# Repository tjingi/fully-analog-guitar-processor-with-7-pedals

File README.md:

## Fishman
- This is a 7-pedal analog guitar processor!
- It features:
- Fuzz Face
- Distortion
- Overdrive
- Phaser
- Flanger
- Delay
- Chorus
Being 100% analog, it delivers a fantastic vintage sound straight out of the 80s and 90s. When designing it, I was heavily inspired by the psychedelic sound of King Gizzard & The Lizard Wizard. Since the enclosure is shaped like a fish, I named it 'Fishman'.

## CAD
- To assemble the enclosure, you will need:
- 27x M3 bolts
- To mount the PCB to the enclosure:
- 4x M3 bolts

  *Made in Fusion 360*

# PCB
Fully designed in KiCad!
<---fuzz face

<----distoshion
<-----overdrive
<----phaser
<----flanger
<----chorus
<-----delay

<---PCB

# BOM

| Component | Value | Quantity |
| :--- | :--- | :---: |
| Capacitor | 5pF | 1 |
| Capacitor | 47pF | 2 |
| Capacitor | 100pF | 4 |
| Capacitor | 150pF | 3 |
| Capacitor | 180pF | 1 |
| Capacitor | 220pF | 2 |
| Capacitor | 330pF | 1 |
| Capacitor | 470pF | 1 |
| Capacitor | 1nF | 4 |
| Capacitor | 2.2nF | 2 |
| Capacitor | 2.7nF | 1 |
| Capacitor | 3.3nF | 1 |
| Capacitor | 3.9nF | 1 |
| Capacitor | 4.7nF | 2 |
| Capacitor | 6.8nF | 2 |
| Capacitor | 8.2nF | 1 |
| Capacitor | 10nF | 11 |
| Capacitor | 12nF | 1 |
| Capacitor | 15nF | 1 |
| Capacitor | 22nF | 2 |
| Capacitor | 33nF | 2 |
| Capacitor | 47nF | 13 |
| Capacitor | 100nF | 6 |
| Capacitor | 220nF | 1 |
| Capacitor | 330nF | 1 |
| Capacitor | 0.47uF | 2 |
| Capacitor | 1uF | 13 |
| Capacitor | 2.2uF | 1 |
| Capacitor | 10uF | 3 |
| Capacitor | 15uF | 1 |
| Capacitor | 20uF | 1 |
| Capacitor | 22uF | 2 |
| Capacitor | 33uF | 3 |
| Capacitor | 47uF | 5 |
| Capacitor | 100uF | 3 |
| Resistor | 33 Ohm | 1 |
| Resistor | 330 Ohm | 1 |
| Resistor | 470 Ohm | 1 |
| Resistor | 1k | 14 |
| Resistor | 1.5k | 1 |
| Resistor | 2k | 1 |
| Resistor | 2.7k | 1 |
| Resistor | 3.3k | 1 |
| Resistor | 4.7k | 8 |
| Resistor | 5.1k | 1 |
| Resistor | 6.8k | 4 |
| Resistor | 10k | 42 |
| Resistor | 12k | 2 |
| Resistor | 20k | 2 |
| Resistor | 22k | 3 |
| Resistor | 24k | 4 |
| Resistor | 27k | 2 |
| Resistor | 33k | 9 |
| Resistor | 39k | 4 |
| Resistor | 47k | 8 |
| Resistor | 56k | 2 |
| Resistor | 68k | 2 |
| Resistor | 82k | 2 |
| Resistor | 100k | 7 |
| Resistor | 120k | 1 |
| Resistor | 150k | 7 |
| Resistor | 180k | 3 |
| Resistor | 220k | 6 |
| Resistor | 330k | 2 |
| Resistor | 360k | 1 |
| Resistor | 470k | 6 |
| Resistor | 1M | 9 |
| Resistor | 2.2M | 1 |
| Resistor | 3.9M | 1 |
| Potentiometer (Alpha) | 10k | 1 |
| Potentiometer (Alpha) | 1M | 1 |
| Potentiometer (Alpha) | A25k | 1 |
| Potentiometer (Alpha) | A50k | 1 |
| Potentiometer (Alpha) | A100k | 1 |
| Potentiometer (Alpha) | A500k | 1 |
| Potentiometer (Alpha) | B1k | 1 |
| Potentiometer (Alpha) | B10k | 1 |
| Potentiometer (Alpha) | B50k | 5 |
| Potentiometer (Alpha) | B100k | 1 |
| Potentiometer (Alpha) | C50k | 1 |
| Potentiometer (Alpha) | C250k | 1 |
| Potentiometer (Alpha) | C500k | 2 |
| Trimmer Potentiometer (RM-065) | 20k | 2 |
| Trimmer Potentiometer (RM-065) | B50k | 1 |
| Trimmer Potentiometer (RM-065) | 100k | 1 |
| Trimmer Potentiometer (RM-065) | 250k | 1 |
| Trimmer Potentiometer (RM-065) | 500k | 1 |
| Integrated Circuit | TL062 | 1 |
| Integrated Circuit | TL071 | 3 |
| Integrated Circuit | TL072 | 1 |
| Integrated Circuit | LM358 | 1 |
| Integrated Circuit | LM741 | 6 |
| Integrated Circuit | RC4558 | 3 |
| Integrated Circuit | MN3007 | 1 |
| Integrated Circuit | MN3102 | 1 |
| Integrated Circuit | MN3207 | 1 |
| Integrated Circuit | CD4047 | 1 |
| Integrated Circuit | PT2399 | 1 |
| Voltage Regulator | L78L05 | 2 |
| Transistor | 2N3906 | 1 |
| Transistor | 2N5088 | 8 |
| Transistor | 2N5952 | 4 |
| Transistor | 2SA733 | 1 |
| Transistor | 2N2907 | 1 |
| Transistor | BC108B | 1 |
| Transistor | BC109B | 1 |
| Diode | 1N914 | 1 |
| Diode | 1N4001 | 1 |
| Diode | 1N4007 | 1 |
| Diode | 1N4148 | 12 |
| Zener Diode | BZV55B5V1 (5.1V) | 1 |
| LED | 3mm | 7 |
| Audio Jack | 6.35mm (Neutrik NRJ4HH-1) | 2 |
| DC Power Jack | Barrel Jack Switch | 1 |
| Footswitch | 3PDT | 7 |
|PCB "Fishman"| |1|
|3D printed enclosure| | 1|
|M3 screw| 25mm| 27|
|M3 screw|10mm|4|

## Assembly

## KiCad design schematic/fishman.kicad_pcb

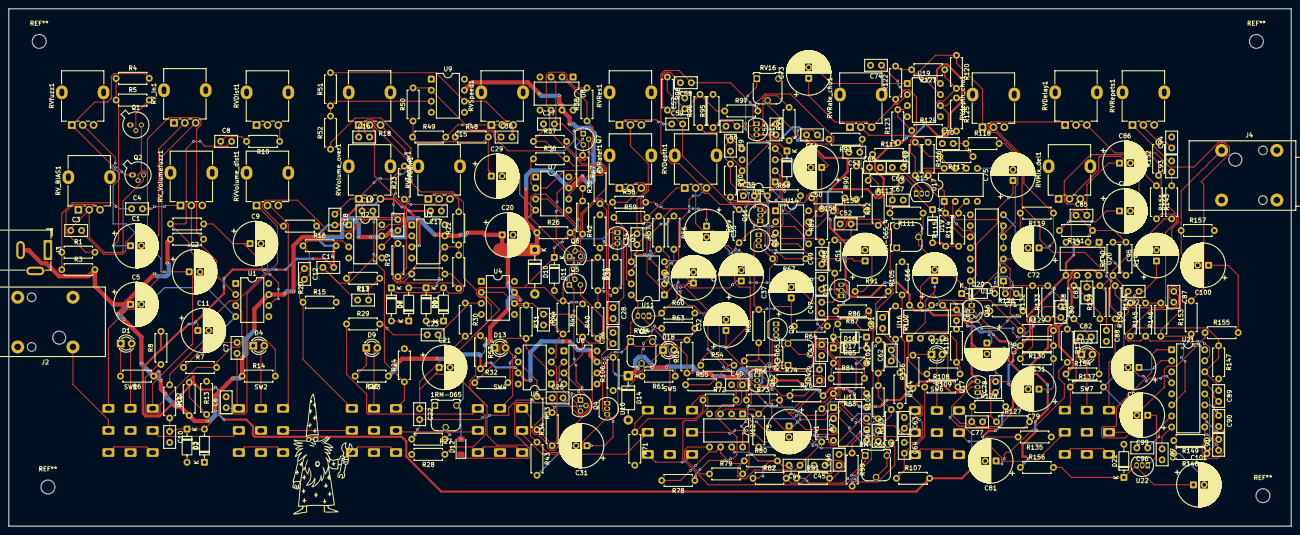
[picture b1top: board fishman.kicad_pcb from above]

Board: 2 copper layers, 295.0 x 119.0 mm, 358 parts (0 on the bottom side), 239 nets.

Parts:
1RM-065: 250K; Potentiometer_Runtron_RM-065_Vertical
C1: 0.47uF; CP_Radial_D10.0mm_P2.50mm
C2: 20uF; CP_Radial_D10.0mm_P2.50mm
C3, C45: 220p; C_Disc_D5.0mm_W2.5mm_P2.50mm
C4: 0.47uF; C_Disc_D5.0mm_W2.5mm_P2.50mm
C5, C101: 100uF; CP_Radial_D10.0mm_P2.50mm
C6, C10, C57, C92: 1n; C_Disc_D5.0mm_W2.5mm_P2.50mm
C7, C23, C30, C34: 10n; C_Disc_D5.0mm_W2.5mm_P2.50mm
C8, C22, C24, C25, C26, C27, C28, C40, C46, C59, C60, C94: 47n; C_Disc_D5.0mm_W2.5mm_P2.50mm
C9, C11, C50, C51: 1u; CP_Radial_D10.0mm_P2.50mm
C12, C13, C14, C18: 0.01uF; C_Disc_D5.0mm_W2.5mm_P2.50mm
C15, C85: 100pF; C_Disc_D5.0mm_W2.5mm_P2.50mm
C16: 0.1uF; C_Disc_D5.0mm_W2.5mm_P2.50mm
C17: 0.01uf; C_Disc_D5.0mm_W2.5mm_P2.50mm
C19: 100nF; C_Disc_D5.0mm_W2.5mm_P2.50mm
C20, C32, C33: 47u; CP_Radial_D10.0mm_P2.50mm
C21, C37: 22u; CP_Radial_D10.0mm_P2.50mm
C29: 15u; CP_Radial_D10.0mm_P2.50mm
C31: 100u; CP_Radial_D10.0mm_P2.50mm
C35, C36: 33u; CP_Radial_D10.0mm_P2.50mm
C38: 5p; C_Disc_D5.0mm_W2.5mm_P2.50mm
C39: 47p; C_Disc_D5.0mm_W2.5mm_P2.50mm
C41: 33uF; CP_Radial_D10.0mm_P2.50mm
C42: 1uf; C_Disc_D5.0mm_W2.5mm_P2.50mm
C43, C61: 6n8; C_Disc_D5.0mm_W2.5mm_P2.50mm
C44, C62: 100p; C_Disc_D5.0mm_W2.5mm_P2.50mm
C47: 12n; C_Disc_D5.0mm_W2.5mm_P2.50mm
C48, C58: 150p; C_Disc_D5.0mm_W2.5mm_P2.50mm
C49, C52: 33n; C_Disc_D5.0mm_W2.5mm_P2.50mm
C53: 3n9; C_Disc_D5.0mm_W2.5mm_P2.50mm
C54: 8n2; C_Disc_D5.0mm_W2.5mm_P2.50mm
C55: 330p; C_Disc_D5.0mm_W2.5mm_P2.50mm
C56: 220n; C_Disc_D5.0mm_W2.5mm_P2.50mm
C63: 1uF; C_Disc_D5.0mm_W2.5mm_P2.50mm
C64: 0.33; C_Disc_D5.0mm_W2.5mm_P2.50mm
C65, C80: 0.01; C_Disc_D5.0mm_W2.5mm_P2.50mm
C66: 1uf; CP_Radial_D10.0mm_P2.50mm
C67: 0.0033; C_Disc_D5.0mm_W2.5mm_P2.50mm
C68: 0.015; C_Disc_D5.0mm_W2.5mm_P2.50mm
C69: 470pF; C_Disc_D5.0mm_W2.5mm_P2.50mm
C70: 0.0047; C_Disc_D5.0mm_W2.5mm_P2.50mm
C71: 150pF; C_Disc_D5.0mm_W2.5mm_P2.50mm
C72, C75, C76: 10uF; CP_Radial_D10.0mm_P2.50mm
C73: 2.2uF; CP_Radial_D10.0mm_P2.50mm
C74: 0.047; C_Disc_D5.0mm_W2.5mm_P2.50mm
C77: 0.0027; C_Disc_D5.0mm_W2.5mm_P2.50mm
C78: 180pF; C_Disc_D5.0mm_W2.5mm_P2.50mm
C79, C81, C84, C86, C95: 1uF; CP_Radial_D10.0mm_P2.50mm
C82, C93: 22n; C_Disc_D5.0mm_W2.5mm_P2.50mm
C83: 47pF; C_Disc_D5.0mm_W2.5mm_P2.50mm
C87, C89: 2n2; C_Disc_D5.0mm_W2.5mm_P2.50mm
C88: 4n7; C_Disc_D5.0mm_W2.5mm_P2.50mm
C90, C91, C96, C97: 100n; C_Disc_D5.0mm_W2.5mm_P2.50mm
C98, C99: 47uF; CP_Radial_D10.0mm_P2.50mm
C100: C_Polarized; CP_Radial_D10.0mm_P2.50mm
D1, D4, D9, D13, D18, D21, D23: LED; LED_D3.0mm
D2, D3, D5, D6, D7, D8, D15, D16, D17, D19, D20, D22: 1N4148; D_DO-35_SOD27_P7.62mm_Horizontal
D10: 1N4007; D_DO-41_SOD81_P10.16mm_Horizontal
D11: 1N914; D_DO-35_SOD27_P7.62mm_Horizontal
D12: BZV55B5V1; D_MiniMELF
D14: 1N4001; D_DO-41_SOD81_P10.16mm_Horizontal
J2, J4: NRJ4HH-1; Jack_6.35mm_Neutrik_NRJ4HH-1_Horizontal
J3: Barrel_Jack_Switch; BarrelJack_GCT_DCJ200-10-A_Horizontal
Q1: BC108B; TO-18-3
Q2: BC109B; TO-18-3
Q3: 2N3906; TO-92_Inline
Q4, Q5, Q6, Q7: 2n5952; TO-92
Q8, Q9, Q10, Q12, Q13, Q14, Q16, Q17: 2n5088; TO-92_Inline
Q11: 2SA733; TO-92_Inline
Q15: 2n2907; TO-92_Inline
R1, R10: 4.7K; R_Axial_DIN0207_L6.3mm_D2.5mm_P7.62mm_Horizontal
R2: 33k; R_Axial_DIN0207_L6.3mm_D2.5mm_P7.62mm_Horizontal
R3: 330; R_Axial_DIN0207_L6.3mm_D2.5mm_P7.62mm_Horizontal
R4, R56, R89, R105, R135, R144, R157: 100K; R_Axial_DIN0207_L6.3mm_D2.5mm_P7.62mm_Horizontal
R5, R6, R14, R22, R25, R53, R72, R106, R108, R134, R136, R143, R154, R155: 1K; R_Axial_DIN0207_L6.3mm_D2.5mm_P7.62mm_Horizontal
R7, R11, R19, R26, R29, R31, R32, R33, R34, R35, R36, R37, R38, R54, R55, R76, R77, R79, R83, R86, R87, R88, R92, R93, R94, R95, R102, R112, R113, R116, R117, R126, R128, R131, R145, R146, R148, R149, R150, R158, R159, R160: 10K; R_Axial_DIN0207_L6.3mm_D2.5mm_P7.62mm_Horizontal
R8, R12, R13, R16, R24, R27, R28, R71, R137: 1M; R_Axial_DIN0207_L6.3mm_D2.5mm_P7.62mm_Horizontal
R9, R30, R51, R61, R73, R121: 470K; R_Axial_DIN0207_L6.3mm_D2.5mm_P7.62mm_Horizontal
R15: 2.2M; R_Axial_DIN0207_L6.3mm_D2.5mm_P7.62mm_Horizontal
R17, R69, R70, R74, R75, R109, R114, R132: 33K; R_Axial_DIN0207_L6.3mm_D2.5mm_P7.62mm_Horizontal
R18, R100: 27K; R_Axial_DIN0207_L6.3mm_D2.5mm_P7.62mm_Horizontal
R20, R23, R110: 6.8K; R_Axial_DIN0207_L6.3mm_D2.5mm_P7.62mm_Horizontal
R21, R57, R64, R81, R107, R130: 220K; R_Axial_DIN0207_L6.3mm_D2.5mm_P7.62mm_Horizontal
R39, R40, R41, R43, R50, R52, R62: 150K; R_Axial_DIN0207_L6.3mm_D2.5mm_P7.62mm_Horizontal
R42, R90: 56K; R_Axial_DIN0207_L6.3mm_D2.5mm_P7.62mm_Horizontal
R44, R45, R46, R47: 24K; R_Axial_DIN0207_L6.3mm_D2.5mm_P7.62mm_Horizontal
R48: 3M9; R_Axial_DIN0207_L6.3mm_D2.5mm_P7.62mm_Horizontal
R49, R60, R65, R67, R68, R85: 4K7; R_Axial_DIN0207_L6.3mm_D2.5mm_P7.62mm_Horizontal
R58: 1K5; R_Axial_DIN0207_L6.3mm_D2.5mm_P7.62mm_Horizontal
R59, R123, R138: 180K; R_Axial_DIN0207_L6.3mm_D2.5mm_P7.62mm_Horizontal
R63, R124: 68K; R_Axial_DIN0207_L6.3mm_D2.5mm_P7.62mm_Horizontal
R66, R91: 330K; R_Axial_DIN0207_L6.3mm_D2.5mm_P7.62mm_Horizontal
R78, R80, R84, R96, R98, R101, R103, R122: 47K; R_Axial_DIN0207_L6.3mm_D2.5mm_P7.62mm_Horizontal
R82, R125: 82K; R_Axial_DIN0207_L6.3mm_D2.5mm_P7.62mm_Horizontal
R97: 22k; R_Axial_DIN0207_L6.3mm_D2.5mm_P7.62mm_Horizontal
R99, R118, R119, R127: 39K; R_Axial_DIN0207_L6.3mm_D2.5mm_P7.62mm_Horizontal
R104: 470R; R_Axial_DIN0207_L6.3mm_D2.5mm_P7.62mm_Horizontal
R111: 3K3; R_Axial_DIN0207_L6.3mm_D2.5mm_P7.62mm_Horizontal
R115, R142: 12K; R_Axial_DIN0207_L6.3mm_D2.5mm_P7.62mm_Horizontal
R120: 120K; R_Axial_DIN0207_L6.3mm_D2.5mm_P7.62mm_Horizontal
R129, R140: 22K; R_Axial_DIN0207_L6.3mm_D2.5mm_P7.62mm_Horizontal
R133: 6K8; R_Axial_DIN0207_L6.3mm_D2.5mm_P7.62mm_Horizontal
R139: 360K; R_Axial_DIN0207_L6.3mm_D2.5mm_P7.62mm_Horizontal
R141, R147: 20K; R_Axial_DIN0207_L6.3mm_D2.5mm_P7.62mm_Horizontal
R151: 5K1; R_Axial_DIN0207_L6.3mm_D2.5mm_P7.62mm_Horizontal
R152: 2K; R_Axial_DIN0207_L6.3mm_D2.5mm_P7.62mm_Horizontal
R153: 2K7; R_Axial_DIN0207_L6.3mm_D2.5mm_P7.62mm_Horizontal
R156: 33; R_Axial_DIN0207_L6.3mm_D2.5mm_P7.62mm_Horizontal
RM-065_2: 500K; Potentiometer_Runtron_RM-065_Vertical
RM-065_3: 20K; Potentiometer_Runtron_RM-065_Vertical
RM-065_4: 100K; Potentiometer_Runtron_RM-065_Vertical
RV14: B50K; Potentiometer_Runtron_RM-065_Vertical
RV16: 20K; Potentiometer_Runtron_RM-065_Vertical
RVDelay1: B50K; Potentiometer_Alpha_RD901F-40-00D_Single_Vertical
RVDepth1: B50K; Potentiometer_Alpha_RD901F-40-00D_Single_Vertical
RVDist1: C500K; Potentiometer_Alpha_RD901F-40-00D_Single_Vertical
RVGain1: B100K; Potentiometer_Alpha_RD901F-40-00D_Single_Vertical
RVMix_del1: B50K; Potentiometer_Alpha_RD901F-40-00D_Single_Vertical
RVRate_cho1: 1M; Potentiometer_Alpha_RD901F-40-00D_Single_Vertical
RVRatef1: C250K; Potentiometer_Alpha_RD901F-40-00D_Single_Vertical
RVRepets1: B50K; Potentiometer_Alpha_RD901F-40-00D_Single_Vertical
RVRes1: C50K; Potentiometer_Alpha_RD901F-40-00D_Single_Vertical
RVSpeed1: C500K; Potentiometer_Alpha_RD901F-40-00D_Single_Vertical
RVTone_ov1: A25K; Potentiometer_Alpha_RD901F-40-00D_Single_Vertical
RVVolume_dist1: A50K; Potentiometer_Alpha_RD901F-40-00D_Single_Vertical
RVVolume_over1: A100K; Potentiometer_Alpha_RD901F-40-00D_Single_Vertical
RV_BIAS1: B10K; Potentiometer_Alpha_RD901F-40-00D_Single_Vertical
RV_In1: B50K; Potentiometer_Alpha_RD901F-40-00D_Single_Vertical
RV_Volumefuzz1: A500K; Potentiometer_Alpha_RD901F-40-00D_Single_Vertical
RVdepth_cho1: 10K; Potentiometer_Alpha_RD901F-40-00D_Single_Vertical
RVfuzz1: B1K; Potentiometer_Alpha_RD901F-40-00D_Single_Vertical
SW1, SW2, SW3, SW4, SW5, SW6, SW7: 3PTD
U1, U2, U3: TL071; DIP-8_W7.62mm
U4, U5, U6, U7, U8, U9: LM741; DIP-8_W7.62mm
U10, U22: L78L05_TO92; TO-92_Inline
U11: TL062; DIP-8_W7.62mm
U12, U13, U16: RC4558; DIP-8_W7.62mm
U14: MN3207; DIP-8_W7.62mm
U15: MN3102; DIP-8_W7.62mm
U17: MN3007; DIP-8_W7.62mm
U18: 4047; DIP-14_W7.62mm
U19: LM358; DIP-8_W7.62mm
U20: TL072; DIP-8_W7.62mm
U21: PT2399; DIP-16_W7.62mm
o: LOGO

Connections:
67: C41.1, R73.2, R74.2, R75.1, R79.2, R83.2, R91.2, U12.3 (+), U13.3 (+)
+4.5: C11.1, C14.2, C17.2, C18.2, C65.1, R8.2, R12.2, R13.1, R16.2, R107.2, R130.2, RVVolume_over1.3, U3.3 (+), U16.5 (+), U20.3 (+), U20.5 (+)
+5V: C32.1, Q8.3 (C), Q11.1 (E), R54.1, R62.1, R69.1, RM-065_2.1, RV14.1, RV16.1, U10.1 (VO), U11.8 (V+), U14.5 (VDD), U15.1 (VDD)
+9V: C5.1, C20.1, C31.1, D10.1 (K), D14.1 (K), J3.2, Q12.3 (C), Q13.3 (C), Q14.3 (C), Q16.3 (C), Q17.3 (C), R2.1, R3.2, R6.1, R12.1, R14.1, R25.1, R26.1, R53.2, R74.1, R76.2, R106.2, R123.1, R126.1, R136.1, R154.1, R156.1, U1.7 (V+), U2.7 (V+), U3.7 (V+), U4.7 (V+), U5.7 (V+), U6.7 (V+), U7.7 (V+), U8.7 (V+), U9.7 (V+), U10.3 (VI), U12.8 (V+), U13.8 (V+), U16.8 (V+), U19.8 (V+), U20.8 (V+)
Distorshion out: SW2.6, SW3.4
GND: 1RM-065.3, C2.2, C5.2, C6.2, C10.2, C11.2, C20.2, C21.2, C29.2, C31.2, C32.2, C33.2, C37.2, C41.2, C48.2, C50.2, C51.2, C53.2, C55.2, C57.2, C67.2, C69.2, C70.1, C72.2, C74.2, C75.2, C76.2, C78.1, C88.2, C92.2, C94.2, C96.2, C97.2, C98.2, C99.2, C101.2, D2.2 (A), D3.1 (K), D10.2 (A), D11.2 (A), D12.2 (A), D14.2 (A), D22.2 (A), J2.S, J3.1, J4.S, Q1.1 (E), Q9.1 (E), Q10.1 (E), Q15.3 (C), R13.2, R15.2, R24.2, R28.2, R42.2, R43.2, R55.2, R60.2, R61.2, R68.2, R71.2, R75.2, R88.2, R90.2, R95.2, R105.2, R125.2, R128.2, R135.1, R137.2, R144.2, R147.2, R148.2, R149.2, R157.2, RM-065_4.3, RV14.3, RV16.3, RVDist1.1, RVDist1.2, RVMix_del1.1, RVRepets1.3, RVRes1.3, RVVolume_dist1.3, RV_Volumefuzz1.3, RVdepth_cho1.3, RVfuzz1.3, SW1.5, SW2.5, SW3.5, SW4.5, SW5.5, SW6.5, SW7.5, U1.4 (V-), U2.4 (V-), U3.4 (V-), U4.4 (V-), U5.4 (V-), U6.4 (V-), U7.4 (V-), U8.4 (V-), U9.4 (V-), U10.2 (GND), U11.4 (V-), U12.4 (V-), U13.4 (V-), U14.1 (GND), U15.3 (GND), U16.4 (V-), U17.4 (VGG), U17.5 (VDD), U18.7 (VSS), U18.8 (+TRIGGER), U18.9 (EXT_RESET), U18.12 (RETRIGGER), U19.4 (V-), U20.4 (V-), U21.3 (AGND), U22.2 (GND)
unnamed: 1RM-065.2, R27.1
unnamed: C1.1, R4.1, R5.1
unnamed: C1.2, RV_In1.2
unnamed: C2.1, RVfuzz1.2
unnamed: C4.1, R1.1, R3.1
unnamed: C4.2, RV_Volumefuzz1.1
unnamed: C6.1, C7.1, SW2.1
unnamed: C7.2, R7.1
unnamed: C8.1, R10.2
unnamed: C9.1, R9.2, U1.6
unnamed: C9.2, R11.1
unnamed: C12.1, R15.1, SW3.1
unnamed: C13.1, C14.1, R18.1
unnamed: C13.2, R17.1
unnamed: C15.2, RVGain1.2, U2.6
unnamed: C16.1, RVGain1.1
unnamed: C16.2, R19.1
unnamed: C17.1, RVTone_ov1.3
unnamed: C18.1, R23.2, RVVolume_over1.1
unnamed: C19.1, RVVolume_over1.2
unnamed: C23.1, R29.2
unnamed: C25.1, R32.2, R33.1, U5.6
unnamed: C26.1, R34.2, R35.1, U6.6
unnamed: C27.1, R36.2, R37.1, U7.6
unnamed: C29.1, R48.2, R49.1, R50.1
unnamed: C30.2, R51.2, RVSpeed1.3, U9.6
unnamed: C34.2, R57.2, RVRatef1.1, RVRatef1.2, U11.7
unnamed: C35.2, C36.2
unnamed: C36.1, R59.2, RVDepth1.1, U11.1
unnamed: C40.1, R72.2
unnamed: C42.2, C43.1, R78.1
unnamed: C43.2, R77.1
unnamed: C44.2, R80.2, R81.1, R82.1, R103.1, U12.7
unnamed: C45.1, R81.2
unnamed: C45.2, C46.1, R82.2
unnamed: C47.1, R86.2, R87.1
unnamed: C50.1, R89.2, RV16.2
unnamed: C52.1, R90.1, R158.1, R159.2
unnamed: C52.2, R91.1, R92.1
unnamed: C53.1, R92.2, R93.1
unnamed: C54.1, R93.2, R94.1
unnamed: C56.2, R96.1
unnamed: C57.1, R96.2, R97.1, R98.1
unnamed: C58.2, C59.2, R98.2, R100.1, U13.1
unnamed: C59.1, RVRes1.1
unnamed: C60.1, RM-065_3.2, RM-065_3.3
unnamed: C60.2, RVRes1.2
unnamed: C61.2, R102.1
unnamed: C62.2, R101.2, R102.2, R104.1, U12.1
unnamed: C63.1, R104.2
unnamed: C64.1, SW6.1
unnamed: C64.2, R107.1, R108.1
unnamed: C65.2, R110.2
unnamed: C66.1, R109.2, R129.1, U16.1
unnamed: C66.2, R111.1, RM-065_4.2
unnamed: C67.1, R111.2, R112.1
unnamed: C68.1, R112.2, R113.1
unnamed: C70.2, R117.1, R118.1
unnamed: C72.1, R119.1, RVdepth_cho1.2
unnamed: C73.2, R120.1, RVdepth_cho1.1, U19.1
unnamed: C74.1, R122.1, RVRate_cho1.2
unnamed: C77.1, R118.2, R127.1
unnamed: C79.1, R129.2, R130.1, R131.1
unnamed: C80.2, R133.1
unnamed: C81.1, R134.2
unnamed: C82.1, R137.1, SW7.1
unnamed: C82.2, R138.1
unnamed: C83.2, C88.1, R139.2, R140.1, R145.2, R146.2, R151.1, U20.7
unnamed: C84.1, R141.2
unnamed: C84.2, RVMix_del1.2
unnamed: C85.2, C86.1, R142.2, U20.1
unnamed: C86.2, R143.1
unnamed: C92.1, C95.1, R150.2
unnamed: C93.1, R151.2
unnamed: C93.2, RVRepets1.1
unnamed: C94.1, R152.2, RVRepets1.2
unnamed: C95.2, R152.1, RVMix_del1.3
unnamed: C100.1, R155.2
unnamed: C100.2, J4.T, R157.1
unnamed: D1.2 (A), SW1.2
unnamed: D1.1 (K), R6.2
unnamed: C10.1, D2.1 (K), D3.2 (A), R11.2, RVVolume_dist1.1
unnamed: D4.2 (A), SW2.2
unnamed: D4.1 (K), R14.2
unnamed: D5.2 (A), D8.1 (K), R20.2
unnamed: D5.1 (K), D6.2 (A)
unnamed: D6.1 (K), D7.2 (A), R21.2, R22.1, U3.6
unnamed: D7.1 (K), D8.2 (A)
unnamed: D9.2 (A), SW3.2
unnamed: D9.1 (K), R25.2
unnamed: D13.2 (A), SW4.2
unnamed: D13.1 (K), R53.1
unnamed: D15.2 (A), Q11.2 (C), R68.1
unnamed: C39.2, D15.1 (K), R67.1, U15.7 (OX1)
unnamed: D16.2 (A), D17.1 (K), R85.2
unnamed: D16.1 (K), D17.2 (A), R84.2, R86.1, U13.7
unnamed: D18.2 (A), SW5.2
unnamed: D18.1 (K), R106.1
unnamed: D19.2 (A), R114.1, R115.1
unnamed: C68.2, D19.1 (K), Q15.1 (E)
unnamed: D20.2 (A), U18.2 (R)
unnamed: C71.1, D20.1 (K), R119.2, U18.3 (RC_COMMON)
unnamed: D21.2 (A), SW6.2
unnamed: D21.1 (K), R136.2
unnamed: C101.1, D22.1 (K), R156.2, U22.3 (VI)
unnamed: D23.2 (A), SW7.2
unnamed: D23.1 (K), R154.2
unnamed: J2.T, SW1.4
unnamed: Q1.2 (B), R5.2
unnamed: C3.2, Q1.3 (C), Q2.2 (B), R2.2
unnamed: C3.1, Q2.3 (C), RV_BIAS1.2
unnamed: Q2.1 (E), R4.2, RVfuzz1.1
unnamed: Q3.2 (B), R39.2, R40.2, R41.1
unnamed: C28.1, Q3.3 (C), R41.2, R42.1
unnamed: C24.2, Q4.3 (D), R44.1, U5.3 (+)
unnamed: C25.2, Q5.3 (D), R45.1, U6.3 (+)
unnamed: C26.2, Q6.3 (D), R46.1, U7.3 (+)
unnamed: C27.2, Q7.3 (D), R47.1, U8.3 (+)
unnamed: Q8.2 (B), R61.1, R62.2, R63.2
unnamed: Q8.1 (E), R60.1, RVDepth1.3
unnamed: Q9.2 (B), Q9.3 (C), R65.1, R66.2
unnamed: C37.1, Q10.2 (B), R64.2, R65.2
unnamed: Q10.3 (C), R67.2
unnamed: C38.2, Q11.3 (B), R69.2, R70.2
unnamed: C40.2, Q12.2 (B), R73.1
unnamed: C42.1, Q12.1 (E), R76.1
unnamed: C48.1, Q13.2 (B), R87.2
unnamed: C47.2, C49.1, Q13.1 (E), R88.1
unnamed: C55.1, Q14.2 (B), R94.2
unnamed: C54.2, C56.1, Q14.1 (E), R95.1
unnamed: C69.1, Q15.2 (B), R113.2
unnamed: C76.1, Q16.2 (B), R126.2
unnamed: C75.1, Q16.1 (E), R115.2, R116.2, U17.1 (GND), U18.4 (~ASTABLE), U18.5 (ASTABLE), U18.6 (-TRIGGER), U18.14 (VDD)
unnamed: C78.2, Q17.2 (B), R127.2
unnamed: C77.2, C79.2, Q17.1 (E), R128.1
unnamed: R1.2, RV_BIAS1.3
unnamed: R10.1, RVDist1.3
unnamed: R22.2, RVTone_ov1.1
unnamed: R23.1, RVTone_ov1.2
unnamed: R28.1, R29.1, SW4.1
unnamed: R38.2, R39.1, U8.6
unnamed: R49.2, RVSpeed1.1, RVSpeed1.2
unnamed: R58.1, RVRatef1.3
unnamed: R63.1, RV14.2
unnamed: R64.1, RVDepth1.2
unnamed: R66.1, RM-065_2.2, RM-065_2.3
unnamed: R71.1, R72.1, SW5.1
unnamed: R99.2, RM-065_3.1
unnamed: R121.2, R122.2, U19.7
unnamed: R132.2, R133.2, R134.1, U16.7
unnamed: R153.2, RVDelay1.2, RVDelay1.3
unnamed: R155.1, SW7.6
unnamed: RV_In1.3, SW1.1
unnamed: SW1.7, SW1.9
unnamed: SW2.7, SW2.9
unnamed: SW3.7, SW3.9
unnamed: SW4.7, SW4.9
unnamed: SW5.7, SW5.9
unnamed: SW6.7, SW6.9
unnamed: SW7.7, SW7.9
unnamed: R7.2, R8.1, U1.3 (+)
unnamed: C8.2, R9.1, U1.2 (-)
unnamed: C12.2, R16.1, U2.3 (+)
unnamed: C15.1, R17.2, R18.2, RVGain1.3, U2.2 (-)
unnamed: R19.2, R20.1, R21.1, U3.2 (-)
unnamed: C23.2, R30.1, U4.3 (+)
unnamed: C24.1, R31.1, R40.1, U4.2 (-), U4.6
unnamed: R31.2, R32.1, U5.2 (-)
unnamed: R33.2, R34.1, U6.2 (-)
unnamed: R35.2, R36.1, U7.2 (-)
unnamed: R37.2, R38.1, U8.2 (-)
unnamed: R51.1, R52.2, U9.3 (+)
unnamed: C30.1, R50.2, U9.2 (-)
unnamed: C33.1, R54.2, R55.1, R56.2, U11.3 (+)
unnamed: C35.1, R58.2, U11.2 (-)
unnamed: R57.1, R59.1, U11.5 (+)
unnamed: C34.1, R56.1, U11.6 (-)
unnamed: C61.1, C62.1, R100.2, R101.1, R103.2, U12.2 (-)
unnamed: R79.1, U12.5 (+)
unnamed: C44.1, R77.2, R78.2, R80.1, U12.6 (-)
unnamed: C58.1, R97.2, U13.2 (-)
unnamed: R83.1, U13.5 (+)
unnamed: C46.2, R84.1, R85.1, R99.1, U13.6 (-)
unnamed: U14.2 (CP1), U15.2 (CP1)
unnamed: U14.6 (CP2), U15.4 (CP2)
unnamed: C49.2, R89.1, U14.3 (IN)
unnamed: R158.2, U14.7 (OUT1)
unnamed: R159.1, U14.8 (OUT2)
unnamed: C51.1, U14.4 (VGG), U15.8 (VGG_OUT)
unnamed: C38.1, C39.1, R70.1, U15.5 (OX3)
unnamed: R108.2, U16.3 (+)
unnamed: R109.1, R110.1, U16.2 (-)
unnamed: C80.1, R131.2, R132.1, U16.6 (-)
unnamed: U17.2 (CP1), U18.11 (~Q)
unnamed: U17.6 (CP2), U18.10 (Q)
unnamed: R114.2, U17.3 (IN)
unnamed: R117.2, R160.2, U17.7 (OUT1)
unnamed: R116.1, R160.1, U17.8 (OUT2)
unnamed: C71.2, U18.1 (C)
unnamed: R123.2, R124.1, U19.3 (+)
unnamed: C73.1, RVRate_cho1.3, U19.2 (-)
unnamed: R120.2, R121.1, U19.5 (+)
unnamed: R124.2, R125.1, U19.6 (-)
unnamed: C85.1, R140.2, R141.1, R142.1, U20.2 (-)
unnamed: C83.1, R138.2, R139.1, U20.6 (-)
unnamed: C97.1, U21.8 (CC0)
unnamed: C96.1, U21.7 (CC1)
unnamed: RVDelay1.1, U21.4 (DGND)
unnamed: C87.1, R145.1, U21.16 (LPF1-IN)
unnamed: C87.2, R146.1, U21.15 (LPF1-OUT)
unnamed: C89.2, R148.1, U21.13 (LPF2-IN)
unnamed: C89.1, R147.1, R150.1, U21.14 (LPF2-OUT)
unnamed: C91.2, U21.10 (OP1-IN)
unnamed: C91.1, U21.9 (OP1-OUT)
unnamed: C90.1, U21.11 (OP2-IN)
unnamed: C90.2, R149.1, U21.12 (OP2-OUT)
unnamed: C98.1, U21.2 (REF)
unnamed: C99.1, U21.1 (VCC), U22.1 (VO)
unnamed: R153.1, U21.6 (VCO)
Over out: SW3.6, SW4.4
VAA: 1RM-065.1, C21.1, C22.1, D11.1 (K), D12.1 (K), Q3.1 (E), Q4.2 (S), Q5.2 (S), Q6.2 (S), Q7.2 (S), R26.2, R30.2, R44.2, R45.2, R46.2, R47.2, R52.1
VEE: C22.2, Q4.1 (G), Q5.1 (G), Q6.1 (G), Q7.1 (G), R27.2, R48.1
cho out: C81.2, R135.2, SW6.3
chorus out: SW6.6, SW7.4
del out: R143.2, R144.1, SW7.3
fla out: C63.2, R105.1, SW5.3
flanger out: SW5.6, SW6.4
fuzz out: RV_Volumefuzz1.2, SW1.3
out dist: RVVolume_dist1.2, SW2.3
out fuzz face: SW1.6, SW2.4
ov out: C19.2, R24.1, SW3.3
pha out: C28.2, R43.1, SW4.3
phase 90 out: SW4.6, SW5.4
